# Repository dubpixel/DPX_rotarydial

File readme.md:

read.me

this is a collection of 'rotarydial' repos/links
 that were on blogs or otherwise scattered on bitbucket - 
 ultimately the starting point for a DPX pulse to DTMF board.

Matt Millman
https://www.mattmillman.com/projects/building-your-own-pulse-to-tone-converter/

http://boris0.blogspot.com/2013/09/rotary-dial-for-digital-age.html

Arnie Weber
https://bitbucket.org/310weber/rotary_dial/src

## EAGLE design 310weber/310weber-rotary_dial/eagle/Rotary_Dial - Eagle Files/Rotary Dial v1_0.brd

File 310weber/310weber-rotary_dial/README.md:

# ARCHIVED - moved to https://github.com/310weber/rotary_dial #

## Rotary phone Pulse to DTMF Converter ##
AVR code for ATTiny85 which counts pulses from a rotary phone dialer and outputs the corresponding DTMF tone on the phone line. 

Modified from the original work by Boris Cherkasskiy - [http://boris0.blogspot.ca/2013/09/rotary-dial-for-digital-age.html](http://boris0.blogspot.ca/2013/09/rotary-dial-for-digital-age.html)

Modified by Arnie Weber.  GPL license, all text above and below must be included in any redistribution

THIS SOFTWARE IS PROVIDED BY THE COPYRIGHT HOLDERS AND CONTRIBUTORS "AS IS" AND ANY EXPRESS OR IMPLIED WARRANTIES, INCLUDING, BUT NOT LIMITED TO, THE IMPLIED WARRANTIES OF MERCHANTABILITY AND FITNESS FOR A PARTICULAR PURPOSE ARE DISCLAIMED. IN NO EVENT SHALL BE LIABLE FOR ANY DIRECT, INDIRECT, INCIDENTAL, SPECIAL, EXEMPLARY, OR CONSEQUENTIAL DAMAGES (INCLUDING, BUT NOT LIMITED TO, PROCUREMENT OF SUBSTITUTE GOODS OR SERVICES; LOSS OF USE, DATA, OR PROFITS; OR BUSINESS INTERRUPTION) HOWEVER CAUSED AND ON ANY THEORY OF LIABILITY, WHETHER IN CONTRACT, STRICT LIABILITY, OR TORT (INCLUDING NEGLIGENCE OR OTHERWISE) ARISING IN ANY WAY OUT OF THE USE OF THIS SOFTWARE, EVEN IF ADVISED OF THE POSSIBILITY OF SUCH DAMAGE.

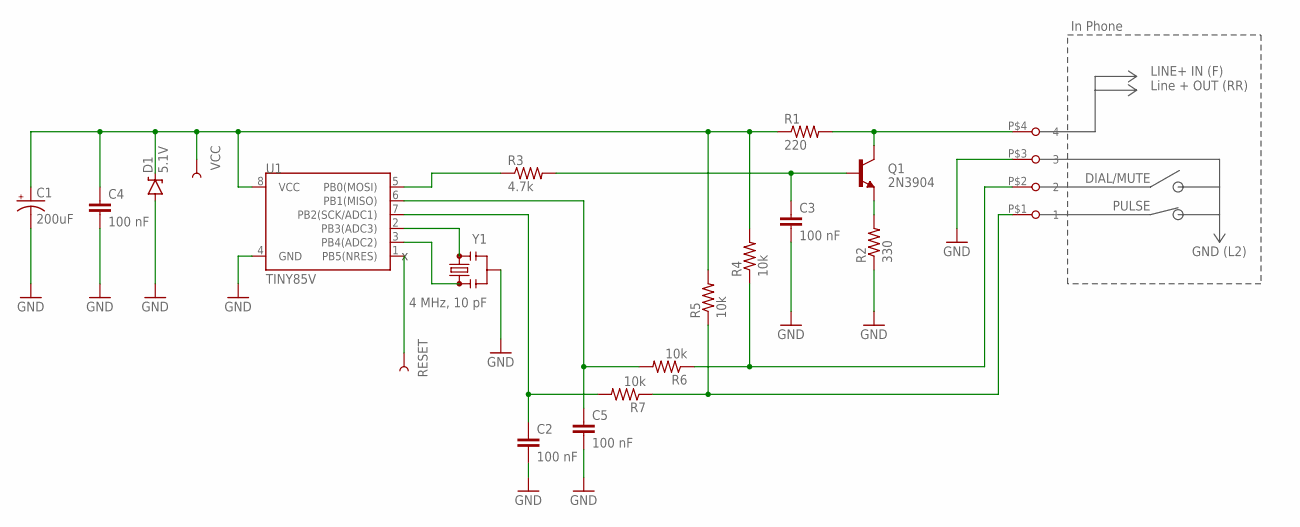
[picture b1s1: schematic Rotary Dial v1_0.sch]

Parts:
C1: 200uF; CPOL-RADIAL-100UF-25V
C2, C3, C4, C5: 100 nF; CAP-PTH-SMALL
D1: 5.1V; DIODE-ZENER
J1: SCREW_TERMINAL_4; .325_TERMINAL_4-PIN
Q1: 2N3904; TO-92-AMMO
R1: 220; AXIAL-0.1
R2: 330; AXIAL-0.1
R3: 4.7k; AXIAL-0.1
R4, R5, R6, R7: 10k; AXIAL-0.1
RESET: TEST-POINTTP_15TH_THRU; TP_15TH
U1: TINY85V; DIP08
VCC: TEST-POINTTP_15TH_THRU; TP_15TH
Y1: 4 MHz, 10 pF; RESONATOR-PTH

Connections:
DIAL/MUTE: J1.P$2 (2), R4.P$1 (1), R6.P$1 (1)
DTMF: R3.P$1 (1), U1.5 (PB0(MOSI))
DTMF': C3.1, Q1.2 (B), R3.P$2 (2)
GND: C1.2 (-), C2.2, C3.2, C4.2, C5.2, D1.P$2 (A), J1.P$3 (3), R2.P$1 (1), U1.4 (GND), Y1.2
LINE_IN: J1.P$4 (4), Q1.3 (C), R1.P$2 (2)
MUTE/DIAL': C5.1, R6.P$2 (2), U1.6 (PB1(MISO))
unnamed: Q1.1 (E), R2.P$2 (2)
unnamed: U1.2 (PB3(ADC3)), Y1.3
unnamed: U1.3 (PB4(ADC2)), Y1.1
PULSE: J1.P$1 (1), R5.P$1 (1), R7.P$1 (1)
PULSE': C2.1, R7.P$2 (2), U1.7 (PB2(SCK/ADC1))
RESET: RESET.P$1, U1.1 (PB5(NRES))
VCC: C1.1 (+), C4.1, D1.P$1 (C), R1.P$1 (1), R4.P$2 (2), R5.P$2 (2), U1.8 (VCC), VCC.P$1

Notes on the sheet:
LINE+ IN (F) Line + OUT (RR)
DIAL/MUTE
PULSE
In Phone
GND (L2)

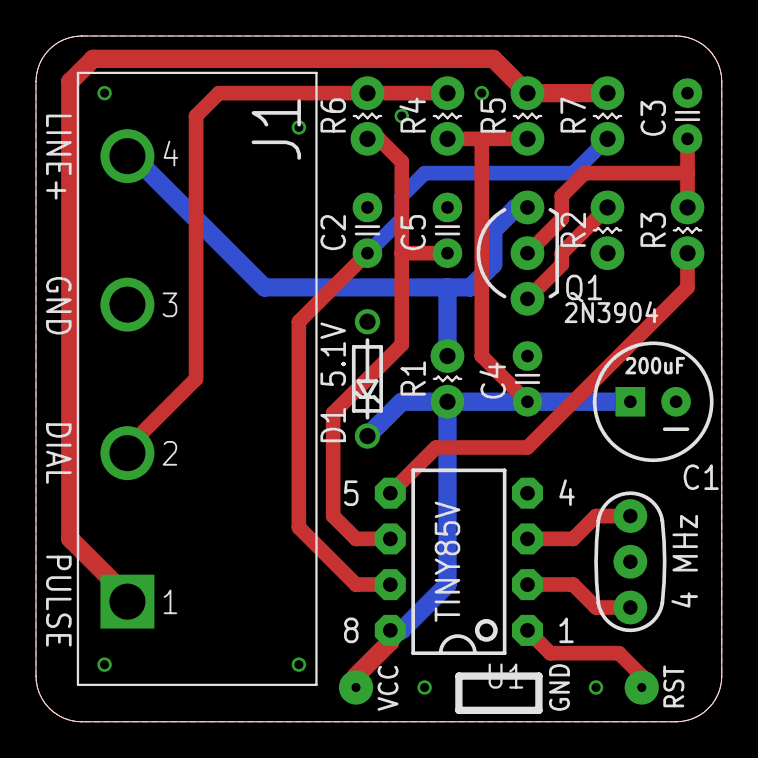
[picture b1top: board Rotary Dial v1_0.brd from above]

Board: 2 copper layers, 38.1 x 38.1 mm, 19 parts (0 on the bottom side), 13 nets.

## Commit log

2023-09-10 reorg, combine, add
    reorg, add inaxeon gerbers and schematic, source bin and eagle of weber,

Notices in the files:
parts and their libraries:
SparkFun-Capacitors: Licensing: Creative Commons ShareAlike 4.0 International - https://creativecommons.org/licenses/by-sa/4.0
